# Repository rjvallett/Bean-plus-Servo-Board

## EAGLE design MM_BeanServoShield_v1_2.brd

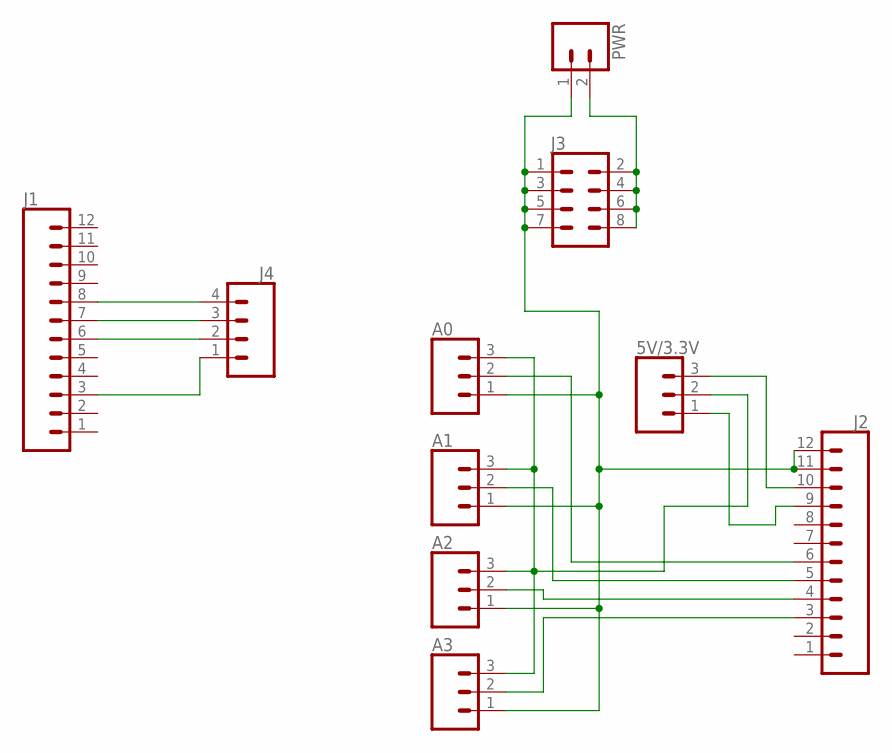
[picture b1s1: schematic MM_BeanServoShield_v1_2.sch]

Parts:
5V/3.3V: CONN_03; 1X03
A0, A1, A2, A3: CONN_03POLAR; MOLEX-1X3
J1, J2: CONN_12; 1X12
J3: CONN_04X2; 2X4
J4: CONN_04; 1X04
PWR: CONN_02POLAR; MOLEX-1X2

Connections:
unnamed: J1.3, J4.1
unnamed: J1.6, J4.2
unnamed: J1.7, J4.3
unnamed: J1.8, J4.4
unnamed: A0.2, J2.6
unnamed: A1.2, J2.5
unnamed: A2.2, J2.4
unnamed: A3.2, J2.3
unnamed: 5V/3.3V.2, A0.3, A1.3, A2.3, A3.3
unnamed: 5V/3.3V.3, J2.10
unnamed: 5V/3.3V.1, J2.9
unnamed: A0.1, A1.1, A2.1, A3.1, J2.11, J2.12, J3.1, J3.3, J3.5, J3.7, PWR.1
unnamed: J3.2, J3.4, J3.6, J3.8, PWR.2

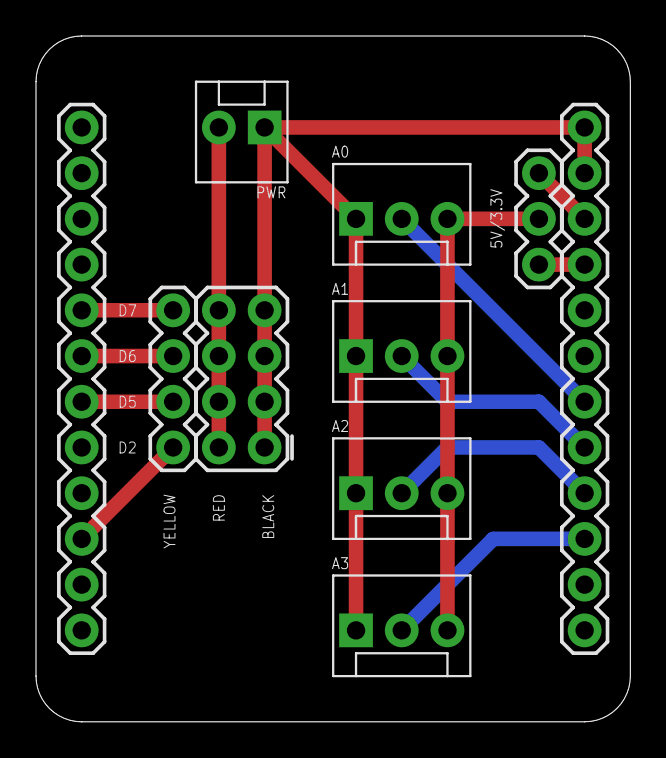
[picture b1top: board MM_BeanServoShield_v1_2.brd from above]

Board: 2 copper layers, 33.0 x 38.1 mm, 10 parts (0 on the bottom side), 13 nets.

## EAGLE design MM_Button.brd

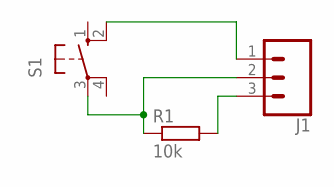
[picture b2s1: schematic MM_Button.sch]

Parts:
J1: CONN_03POLAR; MOLEX-1X3
R1: 10k; 0204/7
S1: 10-XX; B3F-10XX

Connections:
unnamed: J1.3, R1.2
unnamed: J1.2, R1.1, S1.3
unnamed: J1.1, S1.2 (S1)

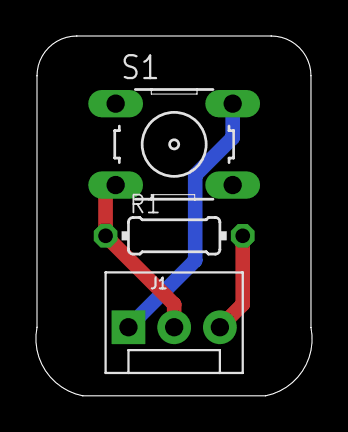
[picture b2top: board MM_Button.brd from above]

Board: 2 copper layers, 15.3 x 20.0 mm, 3 parts (0 on the bottom side), 3 nets.

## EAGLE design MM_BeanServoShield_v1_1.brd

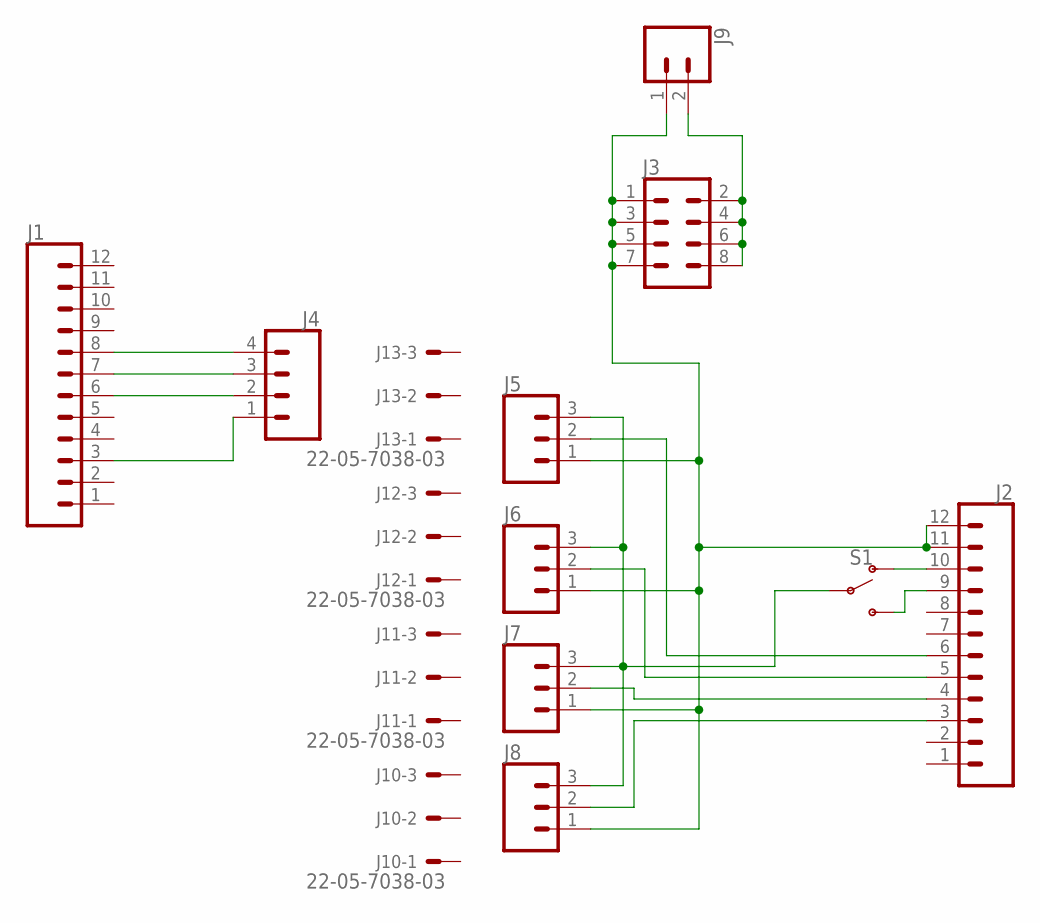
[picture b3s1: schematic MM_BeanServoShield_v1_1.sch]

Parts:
J1, J2: CONN_12; 1X12
J3: CONN_04X2; 2X4
J4: CONN_04; 1X04
J5, J6, J7, J8: CONN_03POLAR; MOLEX-1X3
J9: CONN_02POLAR; MOLEX-1X2
J10, J11, J12, J13: 22-05-7038-03; 7395-03
S1: SWITCH-SPDT-PTH-11.6X4.0MM; SWITCH_SPDT_PTH_11.6X4.0MM

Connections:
unnamed: J1.3, J4.1
unnamed: J1.6, J4.2
unnamed: J1.7, J4.3
unnamed: J1.8, J4.4
unnamed: J2.6, J5.2
unnamed: J2.5, J6.2
unnamed: J2.4, J7.2
unnamed: J2.3, J8.2
unnamed: J5.3, J6.3, J7.3, J8.3, S1.2
unnamed: J2.10, S1.1 (O)
unnamed: J2.9, S1.3 (S)
unnamed: J2.11, J2.12, J3.1, J3.3, J3.5, J3.7, J5.1, J6.1, J7.1, J8.1, J9.1
unnamed: J3.2, J3.4, J3.6, J3.8, J9.2

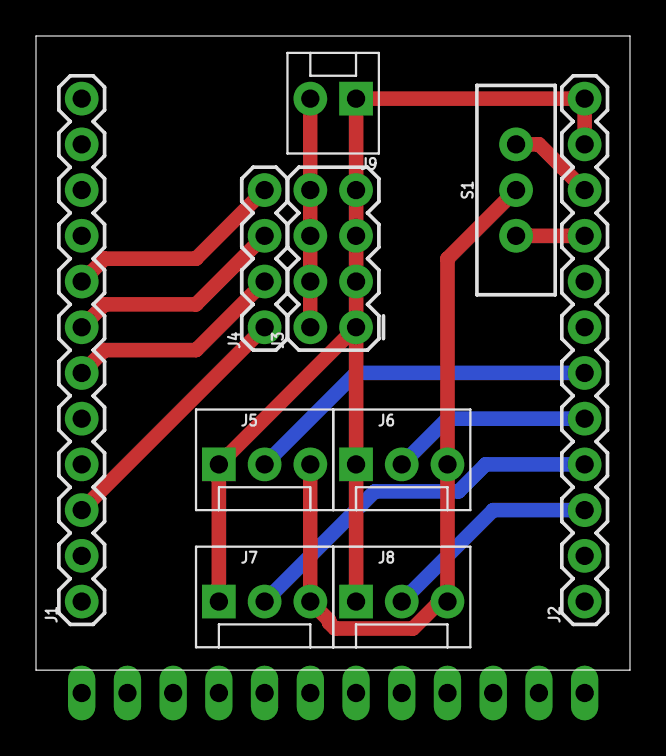
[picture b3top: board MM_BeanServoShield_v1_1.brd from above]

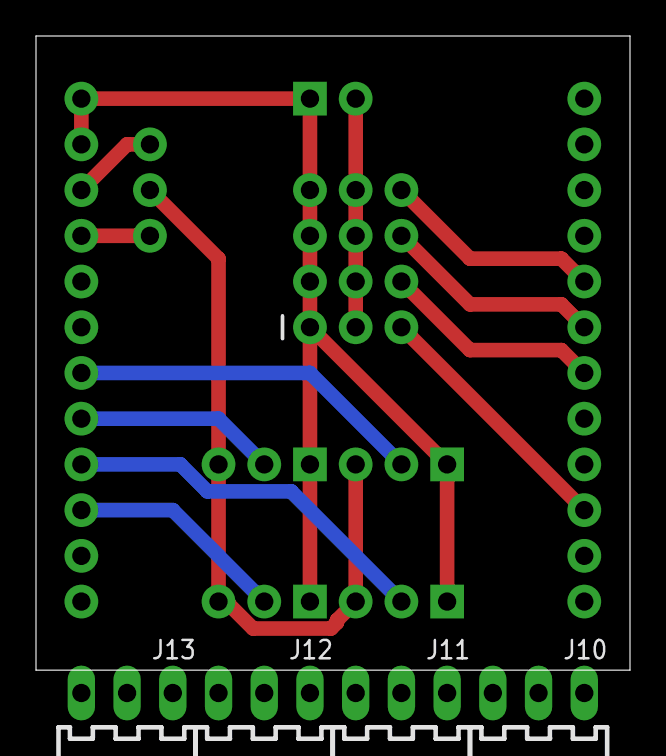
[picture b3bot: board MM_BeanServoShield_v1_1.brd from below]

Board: 2 copper layers, 33.0 x 35.2 mm, 14 parts (4 on the bottom side), 13 nets.

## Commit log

2019-06-27 Initial commit.
2019-06-28 Added updated boards (v1.2)

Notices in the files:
parts and their libraries:
SparkFun-Connectors: Licensing: Creative Commons ShareAlike 4.0 International - https://creativecommons.org/licenses/by-sa/4.0
